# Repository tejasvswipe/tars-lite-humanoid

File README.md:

# TARS-Lite — biped prototype and stationary baseline

A TARS-inspired robotics project organized into exactly four top-level categories: **`PCB/`, `CAD/`, `Firmware/`, and `Docs/`**. The root README and `.gitignore` remain at repository root.

## Repository structure

- [`PCB/`](PCB/) — KiCad source, PCB notes, Gerber/drill manufacturing files and previews.
- [`CAD/`](CAD/) — editable OpenSCAD models, exported STL meshes and print guides.
- [`Firmware/`](Firmware/) — ESP32-S3/Arduino firmware and Raspberry Pi utilities.
- [`Docs/`](Docs/) — build guides, engineering journals, BOMs, wiring maps and visuals, separated into `Biped/`, `Stationary/` and `Media/`.

Each category has its own README index. Files are grouped by design and function within those four folders.

## Biped / 360° head prototype

- [Integrated build guide](Docs/Biped/COMPLETE_BIPED_BUILD.md)
- [Engineering journal](Docs/Biped/BIPED_ENGINEERING_JOURNAL.md)
- [Walking and 360° BOM](Docs/Biped/WALKING_360_BOM.csv) — estimated **$1,128.53–$1,353.93 with 15% contingency**, before shipping/tax.
- [Wiring map](Docs/Biped/BIPED_WIRING.md)
- [Editable add-on CAD](CAD/Biped/biped_tarslite.scad), [print guide](CAD/Biped/BIPED_PRINT_GUIDE.md), and [STL meshes](CAD/Biped/biped_stl/)
- [Neck-interface KiCad board](PCB/DXL-Neck/TARS-Lite-DXL-Neck.kicad_pcb) and [Gerber/drill ZIP](PCB/DXL-Neck/gerber/TARS-Lite-DXL-Neck-Gerbers.zip)
- [ESP32-S3 head/gripper firmware](Firmware/ESP32-Arduino/esp32_biped_head.ino) and [Raspberry Pi console](Firmware/Raspberry-Pi/head_console.py)

The biped lower body relies on a compatible ROBOTIS MINI/Darwin-Mini reference platform and its stock gait controller; vendor CAD and motion files are linked from the [official e-Manual](https://emanual.robotis.com/docs/en/edu/mini/) and are not redistributed here. The add-on design has not been physically assembled or fit-checked. The hand grippers are for very light objects; this is not a general-purpose human-task robot.

The neck uses one additional XL-320 on a separate data bus with AS5600 absolute heading feedback. The neck PCB is not a leg-bus power board. The ESP32-S3 firmware compiles for the `esp32-s3-devkitc-1` PlatformIO target, but has not been flashed or tested on physical hardware. Full PCB DRC/DFM and walking tests remain outstanding. Review the safety gates in the build guide before fabrication or motion.

## Stationary v0.3 baseline

The original tabletop design has fixed support legs and does **not** walk. Its files are kept separate from the biped package:

- [Stationary engineering journal](Docs/Stationary/ENGINEERING_JOURNAL.md)
- [Stationary BOM](Docs/Stationary/BOM.csv)
- [Stationary wiring](Docs/Stationary/WIRING.md)
- [Stationary CAD/STLs](CAD/Stationary/)
- [ServoBus-6 board specification and Gerbers](PCB/ServoBus-6/)

## Repository

Public GitHub repository: [tejasvswipe/tars-lite-humanoid](https://github.com/tejasvswipe/tars-lite-humanoid).

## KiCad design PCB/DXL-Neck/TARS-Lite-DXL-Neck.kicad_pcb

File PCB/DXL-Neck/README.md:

# DYNAMIXEL Neck Interface PCB (1 × XL-320)

Editable board: `TARS-Lite-DXL-Neck.kicad_pcb` (generated by `generate_board.py`). Fabrication outputs: `gerber/`.

## Function

This two-layer board is only the **signal-level bridge and fused power branch for one neck-only XL-320**. It translates ESP32-S3 3.3 V UART to the actuator's 5 V TTL half-duplex DATA line with a 74HCT125 tri-state driver, a 74HCT14 direction inverter, 220 Ω output series resistor, and 10 kΩ / 20 kΩ receive divider. The 74HCT14 makes the library's active-high transmit direction become the 74HCT125's active-low `/OE`; a 10 kΩ pull-down keeps the interface in receive/disabled state during reset. Decoupling capacitors are placed at both logic ICs.

It has a separate 2S actuator input, a PTC fuse (2 A hold) and a fused output to **one** XL-320. Servo power is not sourced from the ESP32 5 V pin. The board is not for the 16-joint leg bus.

## Connector map

| Ref | Pin | Function |
|---|---:|---|
| J1 | 1 | +5 V logic from ESP32 board (not servo power) |
| J1 | 2 | GND |
| J1 | 3 | ESP32 UART TX |
| J1 | 4 | ESP32 UART RX (reduced from DXL DATA) |
| J1 | 5 | DXL direction, high while transmitting |
| J2 | 1 | GND |
| J2 | 2 | Fused 2S servo VDD; actuator must see 6.0–8.4 V |
| J2 | 3 | 5 V TTL DXL DATA |
| J3 | 1 | 2S battery +, through board PTC to J2 pin 2 |
| J3 | 2 | GND |

J2 is a 2.54 mm generic header. Use a correctly keyed, strain-relieved adapter to the XL-320's Molex 53253-0370 interface; verify the manufacturer's GND/VDD/DATA order before connecting. **Never rely on wire colors alone.**

## Power and safety boundaries

- Leg bus remains stock OpenCM + its own manufacturer wiring. The neck DATA line is separate from that leg bus; share only a correctly rated power source/return if the final battery test approves it.
- Fuse the neck branch independently. The XL-320 manual lists 1.1 A stall current at 7.4 V; the included PTC is a starting protection choice, not a substitute for validating the wire, connector, ambient temperature, battery and fuse coordination.
- The board does not contain a regulator for the Pi/ESP32/Arduino or the 5 V hand-servos. Keep positive supply rails separated; make signal grounds common.
- Use a current-limited bench supply for the first actuator test. Do not hot-plug DYNAMIXEL cables.

## Fabrication

Run `/usr/bin/python3 generate_board.py` with KiCad 7's `pcbnew` module, then `./export_gerbers.sh`; the export helper runs `fill_zones.py` in a separate process and saves the filled GND plane before plotting Gerbers. KiCad's connectivity engine reported **0 unconnected items after zone fill**. KiCad 7 in this environment has no CLI DRC command, so a full clearance/width DRC must still be run in the KiCad GUI before fabrication. Also inspect component orientation, thermal clearances, drill map, connector keying and fuse datasheet. This is a prototype: no manufacturer DFM review or powered hardware test has been performed.

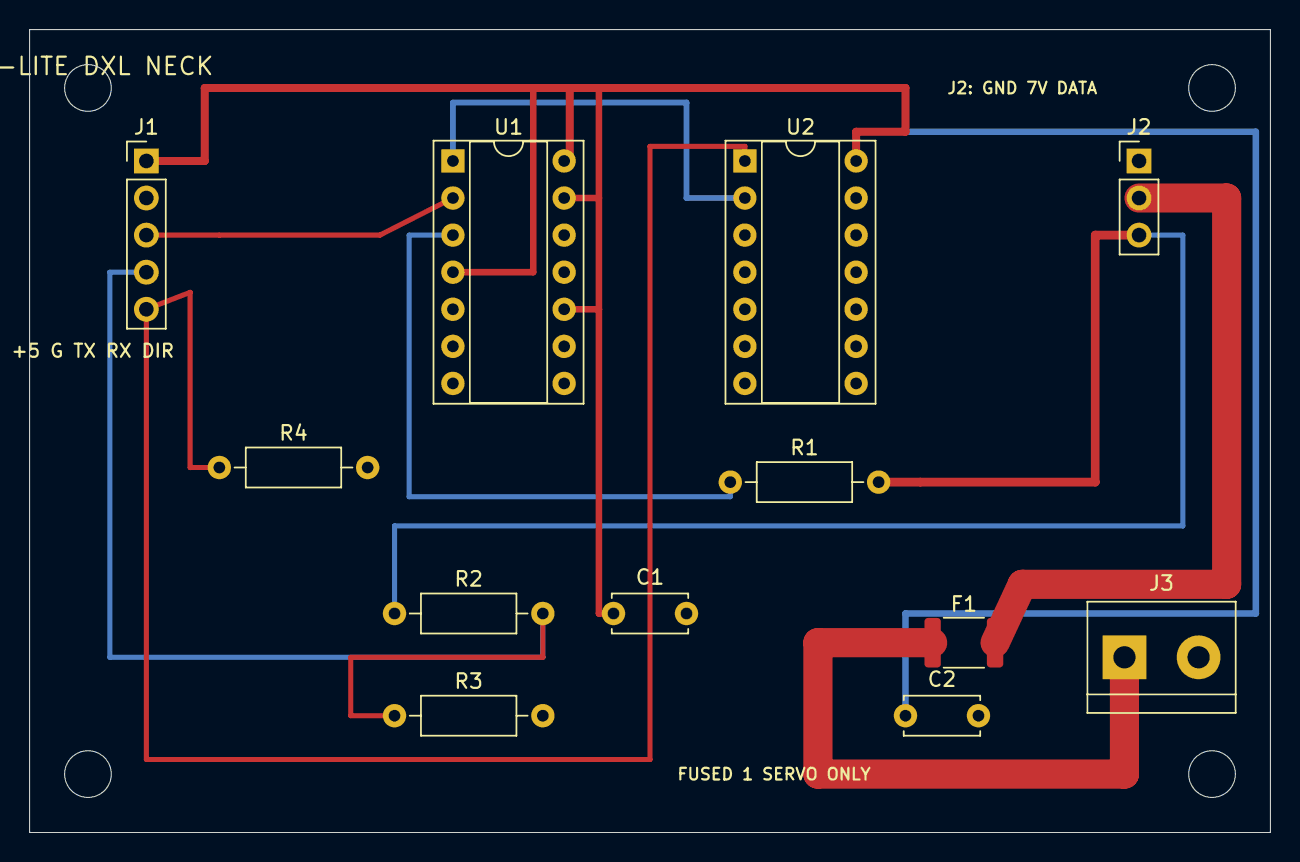
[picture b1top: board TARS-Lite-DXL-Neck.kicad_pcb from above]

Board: 2 copper layers, 85.0 x 55.0 mm, 12 parts (0 on the bottom side), 10 nets.

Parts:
C1, C2: 100nF; C_Disc_D5.0mm_W2.5mm_P5.00mm
F1: PTC 2A HOLD; Fuse_1812_4532Metric
J1: ESP32: 5V/GND/TX/RX/DIR; PinHeader_1x05_P2.54mm_Vertical
J2: XL-320: GND/VDD/DATA; PinHeader_1x03_P2.54mm_Vertical
J3: 2S AUX POWER IN; TerminalBlock_bornier-2_P5.08mm
R1: 220R; R_Axial_DIN0207_L6.3mm_D2.5mm_P10.16mm_Horizontal
R2, R4: 10k; R_Axial_DIN0207_L6.3mm_D2.5mm_P10.16mm_Horizontal
R3: 20k; R_Axial_DIN0207_L6.3mm_D2.5mm_P10.16mm_Horizontal
U1: 74HCT125N; DIP-14_W7.62mm_Socket
U2: 74HCT14N; DIP-14_W7.62mm_Socket

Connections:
+5V_LOGIC: C1.1, C2.1, J1.1, U1.4, U1.10, U1.13, U1.14, U2.14
DXL_DATA: J2.3, R1.2, R2.1
DXL_DIR: J1.5, R4.1, U2.1
DXL_DIR_N: U1.1, U2.2
ESP_RX: J1.4, R2.2, R3.1
ESP_TX: J1.3, U1.2
GND: C1.2, C2.2, J1.2, J2.1, J3.2, R3.2, R4.2, U1.5, U1.7, U1.9, U1.12, U2.3, U2.5, U2.7, U2.9, U2.11, U2.13
TX_STAGE: R1.1, U1.3
VBAT_2S: F1.1, J3.1
V_SERVO: F1.2, J2.2

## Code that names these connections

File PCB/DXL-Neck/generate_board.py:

#!/usr/bin/python3
"""Generate the editable KiCad DYNAMIXEL neck interface PCB (KiCad 7 API).
Logic-only 3.3V UART translator plus fused power branch for ONE XL-320 neck servo.
This does not carry the biped's 16-joint power bus.
"""
from pathlib import Path
import pcbnew

ROOT = Path(__file__).resolve().parent
OUT = ROOT
MM = pcbnew.FromMM
V = pcbnew.VECTOR2I
board = pcbnew.BOARD()
board.SetTitleBlock(pcbnew.TITLE_BLOCK())
board.GetTitleBlock().SetTitle("TARS-Lite DXL Neck Interface — 1x XL-320")
board.GetTitleBlock().SetRevision("1.0")
board.GetTitleBlock().SetComment(0, "Separate data bus; fused single-servo power branch")

NETS = {}
for name in ["GND", "+5V_LOGIC", "ESP_TX", "ESP_RX", "DXL_DIR", "DXL_DIR_N", "TX_STAGE", "DXL_DATA", "VBAT_2S", "V_SERVO"]:
    n = pcbnew.NETINFO_ITEM(board, name)
    board.Add(n)
    NETS[name] = n

def fp(lib, name, ref, val, x, y, rot=0):
    path = Path("/usr/share/kicad/footprints") / (lib + ".pretty")
    obj = pcbnew.FootprintLoad(str(path), name)
    if not obj:
        raise RuntimeError(f"Footprint not found: {path}/{name}")
    obj.SetReference(ref); obj.SetValue(val)
    obj.SetPosition(V(MM(x), MM(y)))
    obj.SetOrientationDegrees(rot)
    board.Add(obj)
    return obj

def pads(obj):
    return {p.GetNumber(): p for p in obj.Pads()}

def net(obj, nums, name):
    for num in nums:
        pads(obj)[str(num)].SetNet(NETS[name])

def xy(pad):
    p = pad.GetPosition()
    return (pcbnew.ToMM(p.x), pcbnew.ToMM(p.y))

def track(a, b, name, width=0.45, layer=pcbnew.F_Cu):
    t = pcbnew.PCB_TRACK(board)
    t.SetStart(V(MM(a[0]), MM(a[1]))); t.SetEnd(V(MM(b[0]), MM(b[1])))
    t.SetWidth(MM(width)); t.SetLayer(layer); t.SetNet(NETS[name])
    board.Add(t)

def route(points, name, width=0.45, layer=pcbnew.F_Cu):
    for a, b in zip(points, points[1:]):
        if abs(a[0]-b[0])+abs(a[1]-b[1]) > 0.001:
            track(a,b,name,width,layer)

def pin(obj, n): return xy(pads(obj)[str(n)])

# Footprints (all real KiCad standard-library parts; through-hole logic parts are hand-solderable).
J1 = fp("Connector_PinHeader_2.54mm", "PinHeader_1x05_P2.54mm_Vertical", "J1", "ESP32: 5V/GND/TX/RX/DIR", 8, 9)
U1 = fp("Package_DIP", "DIP-14_W7.62mm_Socket", "U1", "74HCT125N", 29, 9)
U2 = fp("Package_DIP", "DIP-14_W7.62mm_Socket", "U2", "74HCT14N", 49, 9)
J2 = fp("Connector_PinHeader_2.54mm", "PinHeader_1x03_P2.54mm_Vertical", "J2", "XL-320: GND/VDD/DATA", 76, 9)
J3 = fp("TerminalBlock", "TerminalBlock_bornier-2_P5.08mm", "J3", "2S AUX POWER IN", 75, 43)
R1 = fp("Resistor_THT", "R_Axial_DIN0207_L6.3mm_D2.5mm_P10.16mm_Horizontal", "R1", "220R", 48, 31)
R2 = fp("Resistor_THT", "R_Axial_DIN0207_L6.3mm_D2.5mm_P10.16mm_Horizontal", "R2", "10k", 25, 40)
R3 = fp("Resistor_THT", "R_Axial_DIN0207_L6.3mm_D2.5mm_P10.16mm_Horizontal", "R3", "20k", 25, 47)
R4 = fp("Resistor_THT", "R_Axial_DIN0207_L6.3mm_D2.5mm_P10.16mm_Horizontal", "R4", "10k", 13, 30)
C1 = fp("Capacitor_THT", "C_Disc_D5.0mm_W2.5mm_P5.00mm", "C1", "100nF", 40, 40)
C2 = fp("Capacitor_THT", "C_Disc_D5.0mm_W2.5mm_P5.00mm", "C2", "100nF", 60, 47)
F1 = fp("Fuse", "Fuse_1812_4532Metric", "F1", "PTC 2A HOLD", 64, 42)

# Connector, IC, resistor, fuse and decoupling nets.
net(J1,[1],"+5V_LOGIC"); net(J1,[2],"GND"); net(J1,[3],"ESP_TX"); net(J1,[4],"ESP_RX"); net(J1,[5],"DXL_DIR")
net(U1,[1],"DXL_DIR_N"); net(U1,[2],"ESP_TX"); net(U1,[3],"TX_STAGE"); net(U1,[14],"+5V_LOGIC"); net(U1,[7],"GND")
net(U1,[4,10,13],"+5V_LOGIC") # disable unused buffer channels
net(U1,[5,9,12],"GND")       # unused data inputs are not left floating
net(U2,[1],"DXL_DIR"); net(U2,[2],"DXL_DIR_N"); net(U2,[14],"+5V_LOGIC"); net(U2,[7],"GND")
net(U2,[3,5,9,11,13],"GND")  # unused inverter inputs tied low
net(J2,[1],"GND"); net(J2,[2],"V_SERVO"); net(J2,[3],"DXL_DATA")
net(J3,[1],"VBAT_2S"); net(J3,[2],"GND")
net(R1,[1],"TX_STAGE"); net(R1,[2],"DXL_DATA")
net(R2,[1],"DXL_DATA"); net(R2,[2],"ESP_RX")
net(R3,[1],"ESP_RX"); net(R3,[2],"GND")
net(R4,[1],"DXL_DIR"); net(R4,[2],"GND")
net(C1,[1],"+5V_LOGIC"); net(C1,[2],"GND")
net(C2,[1],"+5V_LOGIC"); net(C2,[2],"GND")
net(F1,[1],"VBAT_2S"); net(F1,[2],"V_SERVO")

# 5V logic rail, separate from 2S servo rail.
route([pin(J1,1),(12,9),(12,4),(37,4),(37,9),pin(U1,14)], "+5V_LOGIC", 0.55)
route([(37,4),(60,4),(60,7),(56.62,7),pin(U2,14)], "+5V_LOGIC", 0.55)
# Tie unused active-low buffer enables high; extend the 5V spine to decouplers.
route([pin(U1,4),(34.5,16.62),(34.5,4),(37,4)], "+5V_LOGIC", 0.45)
route([pin(U1,13),(39,11.54),(39,4)], "+5V_LOGIC", 0.45)
route([pin(U1,10),(39,19.16),(39,11.54)], "+5V_LOGIC", 0.45)
route([pin(C1,1),(39,40),(39,19.16)], "+5V_LOGIC", 0.45)
route([pin(C2,1),(pin(C2,1)[0],40),(84,40),(84,7),(56.62,7),pin(U2,14)], "+5V_LOGIC", 0.45, pcbnew.B_Cu)
# ESP32 UART TX to buffer input.
route([pin(J1,3),(13,14.08),(24,14.08),pin(U1,2)], "ESP_TX", 0.35)
# DXL direction is active-high at the ESP32; 74HCT14 inverts it to active-low /OE.
route([pin(J1,5),(8,50),(42.5,50),(42.5,8),(49,8),pin(U2,1)], "DXL_DIR", 0.35)
# Safe default direction: 10k pulldown; resistor end connects to the same DIR node.
route([pin(J1,5),(11,18),(11,30),pin(R4,1)], "DXL_DIR", 0.35)
# Direction inverter output to buffer /OE on the opposite copper layer.
route([pin(U2,2),(45,pin(U2,2)[1]),(45,5),(29,5),pin(U1,1)], "DXL_DIR_N", 0.4, pcbnew.B_Cu)
# Buffer output → series resistor → DXL bus DATA. Keep this run on B.Cu so it
# does not cross the +5V tie trace for U1's unused /OE pins.
route([pin(U1,3),(26,14.08),(26,32),(48,32),pin(R1,1)], "TX_STAGE", 0.35, pcbnew.B_Cu)
route([pin(R1,2),(61,31),(73,31),(73,14.08),pin(J2,3)], "DXL_DATA", 0.6)
# 10k/20k receive divider reduces the 5V DXL line to about 3.3V at ESP32 RX.
route([pin(J2,3),(79,14.08),(79,34),(pin(R2,1)[0],34),pin(R2,1)], "DXL_DATA", 0.35, pcbnew.B_Cu)
route([pin(R2,2),(pin(R2,2)[0],43),(5.5,43),(5.5,16.62),pin(J1,4)], "ESP_RX", 0.35, pcbnew.B_Cu)
route([pin(R2,2),(pin(R2,2)[0],43),(22,43),(22,47),pin(R3,1)], "ESP_RX", 0.35)
# Fused, single-servo 2S branch. The fuse is not for the 16-joint leg bus.
route([pin(J3,1),(75,51),(54,51),(54,42),pin(F1,1)], "VBAT_2S", 2.0)
route([pin(F1,2),(68,38),(82,38),(82,pin(J2,2)[1]),pin(J2,2)], "V_SERVO", 2.0)

# B.Cu ground plane joins logic ground and servo return at the connector; all GND THT pads attach.
zone = pcbnew.ZONE(board)
zone.SetLayer(pcbnew.B_Cu); zone.SetNet(NETS["GND"])
zone.SetLocalClearance(MM(0.25)); zone.SetThermalReliefGap(MM(0.30)); zone.SetThermalReliefSpokeWidth(MM(0.30))
zone.Outline().NewOutline()
for x,y in [(2,2),(83,2),(83,53),(2,53)]: zone.Outline().Append(MM(x),MM(y))
board.Add(zone)

# Board outline and mounting holes.
outline = pcbnew.PCB_SHAPE(board); outline.SetShape(pcbnew.SHAPE_T_RECT)
outline.SetStart(V(MM(0),MM(0))); outline.SetEnd(V(MM(85),MM(55))); outline.SetLayer(pcbnew.Edge_Cuts); outline.SetWidth(MM(0.05)); board.Add(outline)
for x,y in [(4,4),(81,4),(4,51),(81,51)]:
    h = pcbnew.PCB_SHAPE(board); h.SetShape(pcbnew.SHAPE_T_CIRCLE); h.SetCenter(V(MM(x),MM(y))); h.SetEnd(V(MM(x+1.6),MM(y))); h.SetLayer(pcbnew.Edge_Cuts); h.SetWidth(MM(0.05)); board.Add(h)

def text(txt,x,y,size=1.0):
    t=pcbnew.PCB_TEXT(board); t.SetText(txt); t.SetPosition(V(MM(x),MM(y))); t.SetLayer(pcbnew.F_SilkS); t.SetTextSize(V(MM(size),MM(size))); t.SetTextThickness(MM(0.15)); board.Add(t)
text("TARS-LITE DXL NECK",3,2.5,1.2)
text("J1: +5 G TX RX DIR",3,22,0.9)
text("J2: GND 7V DATA",68,4,0.8)
text("FUSED 1 SERVO ONLY",51,51,0.8)

board_path = OUT / "TARS-Lite-DXL-Neck.kicad_pcb"
pcbnew.SaveBoard(str(board_path), board)
print(board_path)
print(f"Footprints: {len(board.GetFootprints())}, tracks: {len(board.GetTracks())}, zones: {len(board.Zones())}")
